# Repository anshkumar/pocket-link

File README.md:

# Pocket Link

A small USB-C adapter that lets a [Pocket](https://pocketide.com) bot hear and speak on an Android
phone's own calls, and (firmware 0.2) tap and type on the phone for it. The phone sees a USB headset, so Android routes the call's audio to it; a second
channel on the same plug carries that audio to the Pocket app, which streams it to the voice engine over
the phone's own internet. No Bluetooth, no Wi-Fi, no battery, nothing stored on the device.

**This is open hardware.** The board, the firmware, the USB protocol and the test tools are here so that
anyone can see exactly what the thing plugged into their phone does, build one, or make it work on a
phone we have not tried.

```
caller ⇄ phone (cellular / WhatsApp call)
           │  Android routes call audio to the "USB headset"
           ▼
   USB-C ⇄ Pocket Link (RP2040)
           │  interface 1–2: USB Audio (UAC 1.0) headset, mic in / headphones out
           │  interface 3:   vendor bulk data channel
           │  interface 4:   HID touch screen + keyboard (firmware 0.2): the app's taps and keystrokes
           ▼
   Pocket app (USB host API) ⇄ WebSocket ⇄ voice engine
```

| Folder | What |
|---|---|
| `revA/` | The first board: KiCad project, Gerbers, BOM, CPL, STEP, schematic PDF, and `source/design.py`, the generator that is the single source of truth. 31 × 16 mm, 4-layer, board-edge USB-C plug. Proven on real calls (Motorola edge 60, Android 16) on 2026-10-08. |
| `revB/` | The next board: the same circuit as a pod on the back of the phone with a short lead, two layers, under ₹500 to build. Plan and cost model; files follow. |
| `firmware/pocket-link-fw/` | RP2040 firmware (Rust): composite USB headset + data channel + HID touch screen/keyboard, 48 kHz ⇄ 16 kHz resampling, the data protocol. Prebuilt `pocket-link-fw.uf2`. |
| `firmware/pocket-link-fw/PROTOCOL.md` | USB descriptors and the app ⇄ adapter packet protocol. The contract the Pocket app implements. |
| `firmware/tools/` | `link_pc_test.py`: status, two-way loopback test and bootloader entry from a Linux PC. `link_input_bench.py`: tap, swipe and type on the phone through the adapter, over adb. |
| `firmware/hosttest/` | USB descriptor dump and validator; resampler frequency response. |
| `firmware/android-test/` | A bare Android test app (Java, no Gradle) that talks to the adapter and a local voice engine. Useful for bring-up on a new phone. |
| `COMPATIBILITY.md` | Which phones work. Please add yours. |

## Build one (DIY)

You do not need our board. Any RP2040 board works for a first test:

1. Hold BOOT and plug a Raspberry Pi Pico or Waveshare RP2040-Zero into a PC; copy `firmware/pocket-link-fw/pocket-link-fw.uf2` onto the `RPI-RP2` drive.
2. Run `python3 firmware/tools/link_pc_test.py status` (needs `pyusb numpy` and the udev rule in `firmware/README.md`). `loopback` must pass both ways.
3. Connect the board to the phone with a USB-C OTG cable, install the Pocket app, open **Account → Voice → Pocket Link**, and set it up. The app recognises the device by its USB identity.

A Pico on an OTG cable is a working Pocket Link. It is also a lever on your phone's port; the pod in `revB/` exists because of that.

## Licences

- Hardware (`revA/`, `revB/`): **CERN-OHL-P-2.0** (`LICENSE-HARDWARE.txt`). Permissive: build it, sell it, change it, keep the notice.
- Firmware, tools and the test app (`firmware/`): **Apache-2.0** (`LICENSE`). `third_party/usbd-audio` is MIT OR Apache-2.0 by its author, with our patches listed in its `PATCHES.md`.
- "Pocket" and "Pocket Link" are names of Pocket; a clone of the design is welcome, a clone of the name is not.

## USB identity

Rev A ships with the pid.codes **test** ID `1209:0001`. Before a public batch we apply for a real PID at
[pid.codes](https://pid.codes), which allocates them to open-source hardware; `PID-REQUEST.md` is the
application. Until then, anything you build with this firmware carries the test ID, which must not be sold.

## Contributing

Phone reports (`COMPATIBILITY.md`), firmware fixes and alternative boards are all welcome; see
`CONTRIBUTING.md`. Bring-up lessons so far: the headphones stream **must be stereo** (a mono USB output
makes Android 16's mixer abort audioserver), and the app should claim the device through a
`USB_DEVICE_ATTACHED` intent filter so Android offers "always" on the permission prompt.

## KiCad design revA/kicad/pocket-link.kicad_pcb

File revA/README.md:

# Pocket Link — rev A

A small USB-C dongle that plugs into the phone. The phone sees it as a **USB headset**,
so Android routes call audio to it. It also exposes a **data channel** that the Pocket app uses to stream
that audio to and from the voice agent over the phone's own internet.
There is no Bluetooth, no Wi-Fi and no battery.

Status: **design complete, DRC clean, not yet fabricated or tested.**

## Size and cost

* PCB **31 × 16 mm**, 0.8 mm thick. With the plug and a shell, about 36 × 18 × 6 mm.
* Parts: **≈ $2.20 (≈ ₹185) per adapter** at LCSC 100-pc prices.
  Prototype run of 5 assembled at JLCPCB is roughly $40–60 total (PCB + setup + parts + shipping).
  Check the real figure in the JLC quote.

## How it works

```
caller ⇄ phone (cellular / WhatsApp call)
           │  Android routes call audio to the "USB headset"
           ▼
   USB-C ⇄ Pocket Link (RP2040)
           │  interface 1: USB Audio (UAC) headset, 16 kHz mono speaker + mic
           │  interface 2: vendor bulk data
           ▼
   Pocket app (USB host API) ⇄ WebSocket ⇄ voice agent
```

The firmware is a TinyUSB composite device:
* Speaker stream (caller's voice) → forwarded to the app on the data interface.
* Data from the app (agent's voice) → played into the microphone stream, so the caller hears the agent.
* The app answers and hangs up calls itself (Android `ANSWER_PHONE_CALLS`). No ADB needed.

## Circuit (see `docs/Pocket-Link-revA-schematic.pdf`)

| Ref | Part | LCSC | Notes |
|---|---|---|---|
| J1 | Molex 105444-0001 USB-C **plug**, board-edge straddle | C134082 | Alt: SHOU HAN TYPE-C 24P GTJB. **Needs 0.8 mm PCB** |
| U1 | RP2040 | C2040 | USB 1.1 device. Support circuit per the RP2040 hardware design guide |
| U2 | W25Q16JVSNIQ 2 MB QSPI flash | C2456211 | Firmware |
| U3 | AP2112K-3.3 LDO | C51118 | Phone VBUS → 3.3 V, about 25 mA load |
| U4 | USBLC6-2SC6 | C7519 | ESD on D+/D− |
| Y1 | 12 MHz 3225 crystal + 2 × 33 pF, 1 kΩ on XOUT | C9002 | |
| R1 | 5.1 kΩ on CC | C25905 | Tells the phone a USB device is attached, so it supplies 5 V |
| D1 | Green status LED (GPIO25) | C72043 | |
| TP1–3 | Back-side pads: BOOT, GND, 3V3 | — | |

The SWD debug pins are not brought out. Firmware loads over USB, and debugging happens on any
RP2040 dev board running the same firmware.

## Board

* 4 layers, **0.8 mm**: L1 signal, L2 GND, L3 +3V3, L4 signal + GND pour.
* 0.1 mm min clearance and 0.127 mm min track. Both are within JLCPCB's standard 4-layer capability. The
  USB-C plug's 0.5 mm-pitch pads need this.
* 0.3 / 0.6 mm vias. 5 vias in the RP2040 ground pad.
* Verification (`docs/verification.txt`):
  * schematic and PCB both match `source/design.py` (21 nets, 34 parts)
  * KiCad DRC: **0 violations, 0 unconnected**
  * Gerbers re-read independently: 11 layers, outline 31 × 16 mm

## Ordering (JLCPCB)

1. Gerbers: `fab/Pocket-Link-revA-gerbers.zip`. Settings: 4 layers, **0.8 mm thickness**, JLC04081H-3313 stackup (or
   whatever JLC offers for 0.8 mm 4-layer), ENIG recommended for the fine-pitch plug and QFN.
2. Assembly (top side): `fab/BOM_JLCPCB.csv` + `fab/CPL_JLCPCB.csv`. **Check rotations in JLC's preview**,
   especially U1 pin 1, U2, U3, U4, Y1 and D1.
3. **The USB-C plug J1 is not in the JLC BOM or CPL.** It straddles the board edge with pads on both sides,
   so solder it after assembly (hand or hot-air), or ask JLC for manual soldering. Order C134082 along with the
   boards.
4. Small boards: ask JLC to panelize (e.g. 2 × 3) to stay above their minimum assembly size.

## First power-up

1. Plug into a Linux PC first (USB-C to USB-C cable, or a USB-A to USB-C female adapter). A blank board
   shows up as the **RPI-RP2** drive. Drag the firmware `.uf2` onto it.
2. `lsusb` / `aplay -l` should show a USB audio card plus the vendor interface. Run a PC loopback test.
3. Plug into the Motorola, install the Pocket test app, and call it from the allowed number.
4. To re-enter the bootloader later: short **BT** to **G** on the back while plugging in.

## Risks / next steps

| Risk | Plan |
|---|---|
| Whether the app can use the data interface while Android uses the audio part | First firmware test. Fallbacks need firmware changes only (e.g. a HID data channel) |
| Some phones need special USB audio formats (48 kHz) | Firmware offers 48 kHz too and resamples internally |
| Charging through the adapter (v2) | Needs a USB-PD pass-through controller and a female USB-C. Planned for rev B |
| Enclosure | A simple 2-part shell like a USB-C to 3.5 mm adapter, next step after the board fits |

## Files

* `kicad/`: KiCad 7 project with schematic, PCB and local footprints (QFN-56 with 0.3 mm vias)
* `fab/`: Gerbers + drill files, JLC BOM/CPL, full BOM with MPNs and cost, STEP 3D model
* `docs/`: schematic PDF, assembly + layer PDF, top/bottom previews, DRC report, verification results
* `source/`: Python generators. `design.py` is the single source of truth

## Cost reality check (PCB Power quote INQ649465, 7 Oct 2026, 6 boards)

| Line | Quote | Per board | Why |
|---|---|---|---|
| PCB fabrication (4-layer, 0.8 mm, ENIG, 2 panels of 3) | ₹6,966 | ₹1,161 | Panel NRE spread over 6 boards; a 2-layer board would roughly halve this |
| Assembly (30 SMD + 1 QFN, top side) | ₹3,132 | ₹522 | Reasonable for a tiny run |
| Component sourcing (turnkey) | ₹8,950 | ₹1,492 | The outlier. Parts are ≈ $2.20 (≈ ₹185) per board at LCSC; the quote carries minimum pack quantities (32 × 33 pF for 12 used), "independent supplier" markups on the RP2040, flash, crystal and passives (no warranty, 3–5 week lead), one part from Robu, and the LED was **not available and not priced** |
| Total before GST | ₹19,048 | ₹3,175 | ≈ ₹3,750 per adapter with GST, for six |

So the BOM is not the problem; the sourcing route and the batch size are. What to do:

1. **Consign the parts.** Order one LCSC/DigiKey basket yourself (10 sets ≈ ₹1,500 shipped, every part in stock, warranted) and give PCB Power assembly only. That alone cuts the per-board cost from ₹3,175 to about ₹1,900.
2. **Or order at JLCPCB** with the files in `fab/` (4-layer 0.8 mm ENIG, 5 boards + assembly ≈ $40–60 all in, plus Indian customs ≈ ₹1,000–1,500): roughly a quarter of the PCB Power price for the same six boards, because the parts come from their own LCSC shelf.
3. **Rev B goes to two layers** (the board-edge plug is the only reason for four) and a pre-molded cable-mount plug, which removes the one hand-soldered part. Fabrication then drops to the ₹300–500 per board range in tens, and under ₹100 in hundreds.
4. **Don't change the MCU for cost yet.** RP2040 + flash + crystal are ₹90 of the ₹185 parts; CH32X035 saves about ₹60 a board at the price of a firmware port. Worth it at a thousand units, and then for its on-chip USB-PD PHY (charge-through in rev C), not for the ₹60.

## Carrying it without breaking it (stopgap for rev A)

Rev A is a 36 mm rigid body hanging off the phone's USB-C receptacle: a 10 N snag at the tip is a 0.36 N·m moment on the port, enough to crack the plug or the phone's socket. Until rev B (pod on the back of the phone, 6–8 cm lead with strain relief), ship every rev A with a short **USB-C male-to-female extension (≈ 10 cm)**. USB audio and the vendor bulk channel pass through an extension; the dongle then hangs on a cable instead of a lever. Rev C adds a USB-C female for charge-through (PD power-role swap; CH32X035 has the PD PHY on chip).

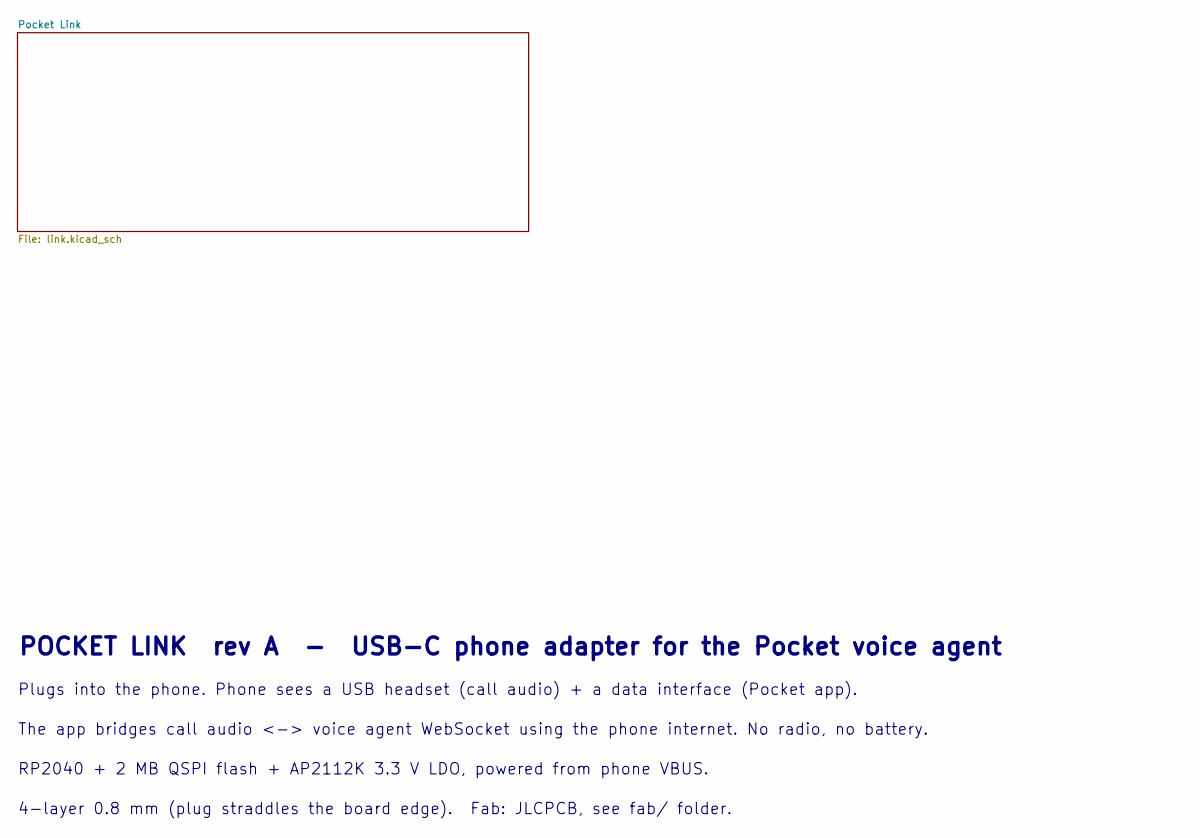
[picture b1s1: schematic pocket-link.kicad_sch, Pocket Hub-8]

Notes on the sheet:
POCKET LINK rev A - USB-C phone adapter for the Pocket voice agent
Plugs into the phone. Phone sees a USB headset (call audio) + a data interface (Pocket app).
The app bridges call audio <-> voice agent WebSocket using the phone internet. No radio, no battery.
RP2040 + 2 MB QSPI flash + AP2112K 3.3 V LDO, powered from phone VBUS.
4-layer 0.8 mm (plug straddles the board edge). Fab: JLCPCB, see fab/ folder.

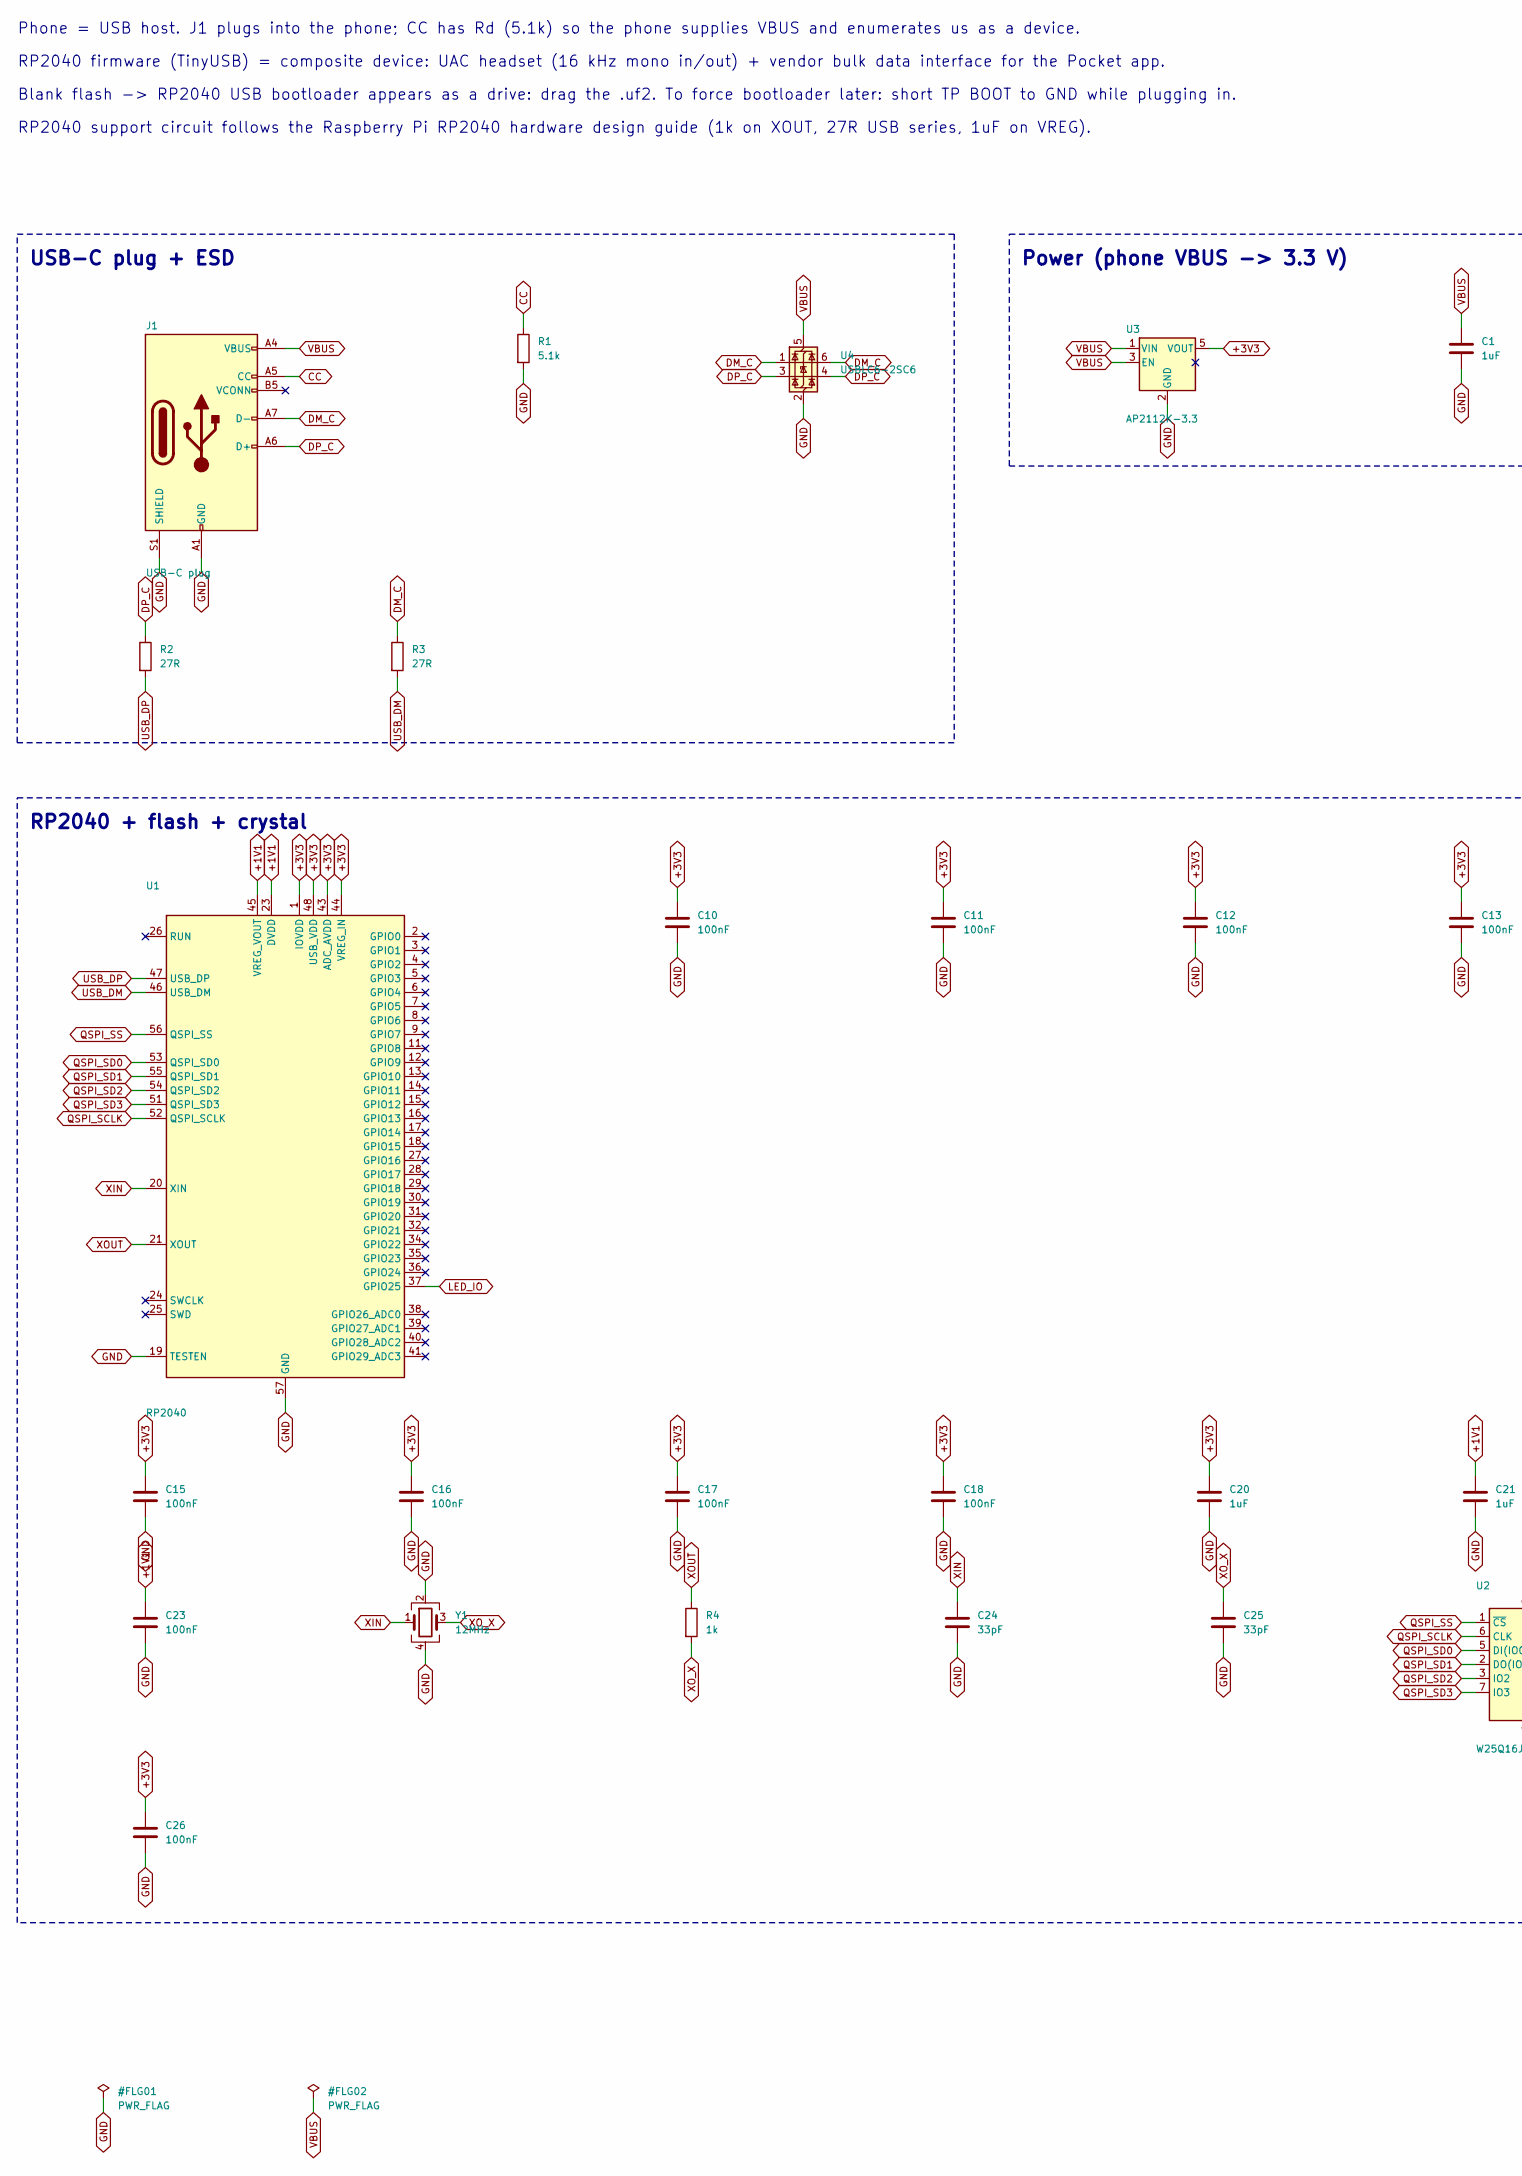
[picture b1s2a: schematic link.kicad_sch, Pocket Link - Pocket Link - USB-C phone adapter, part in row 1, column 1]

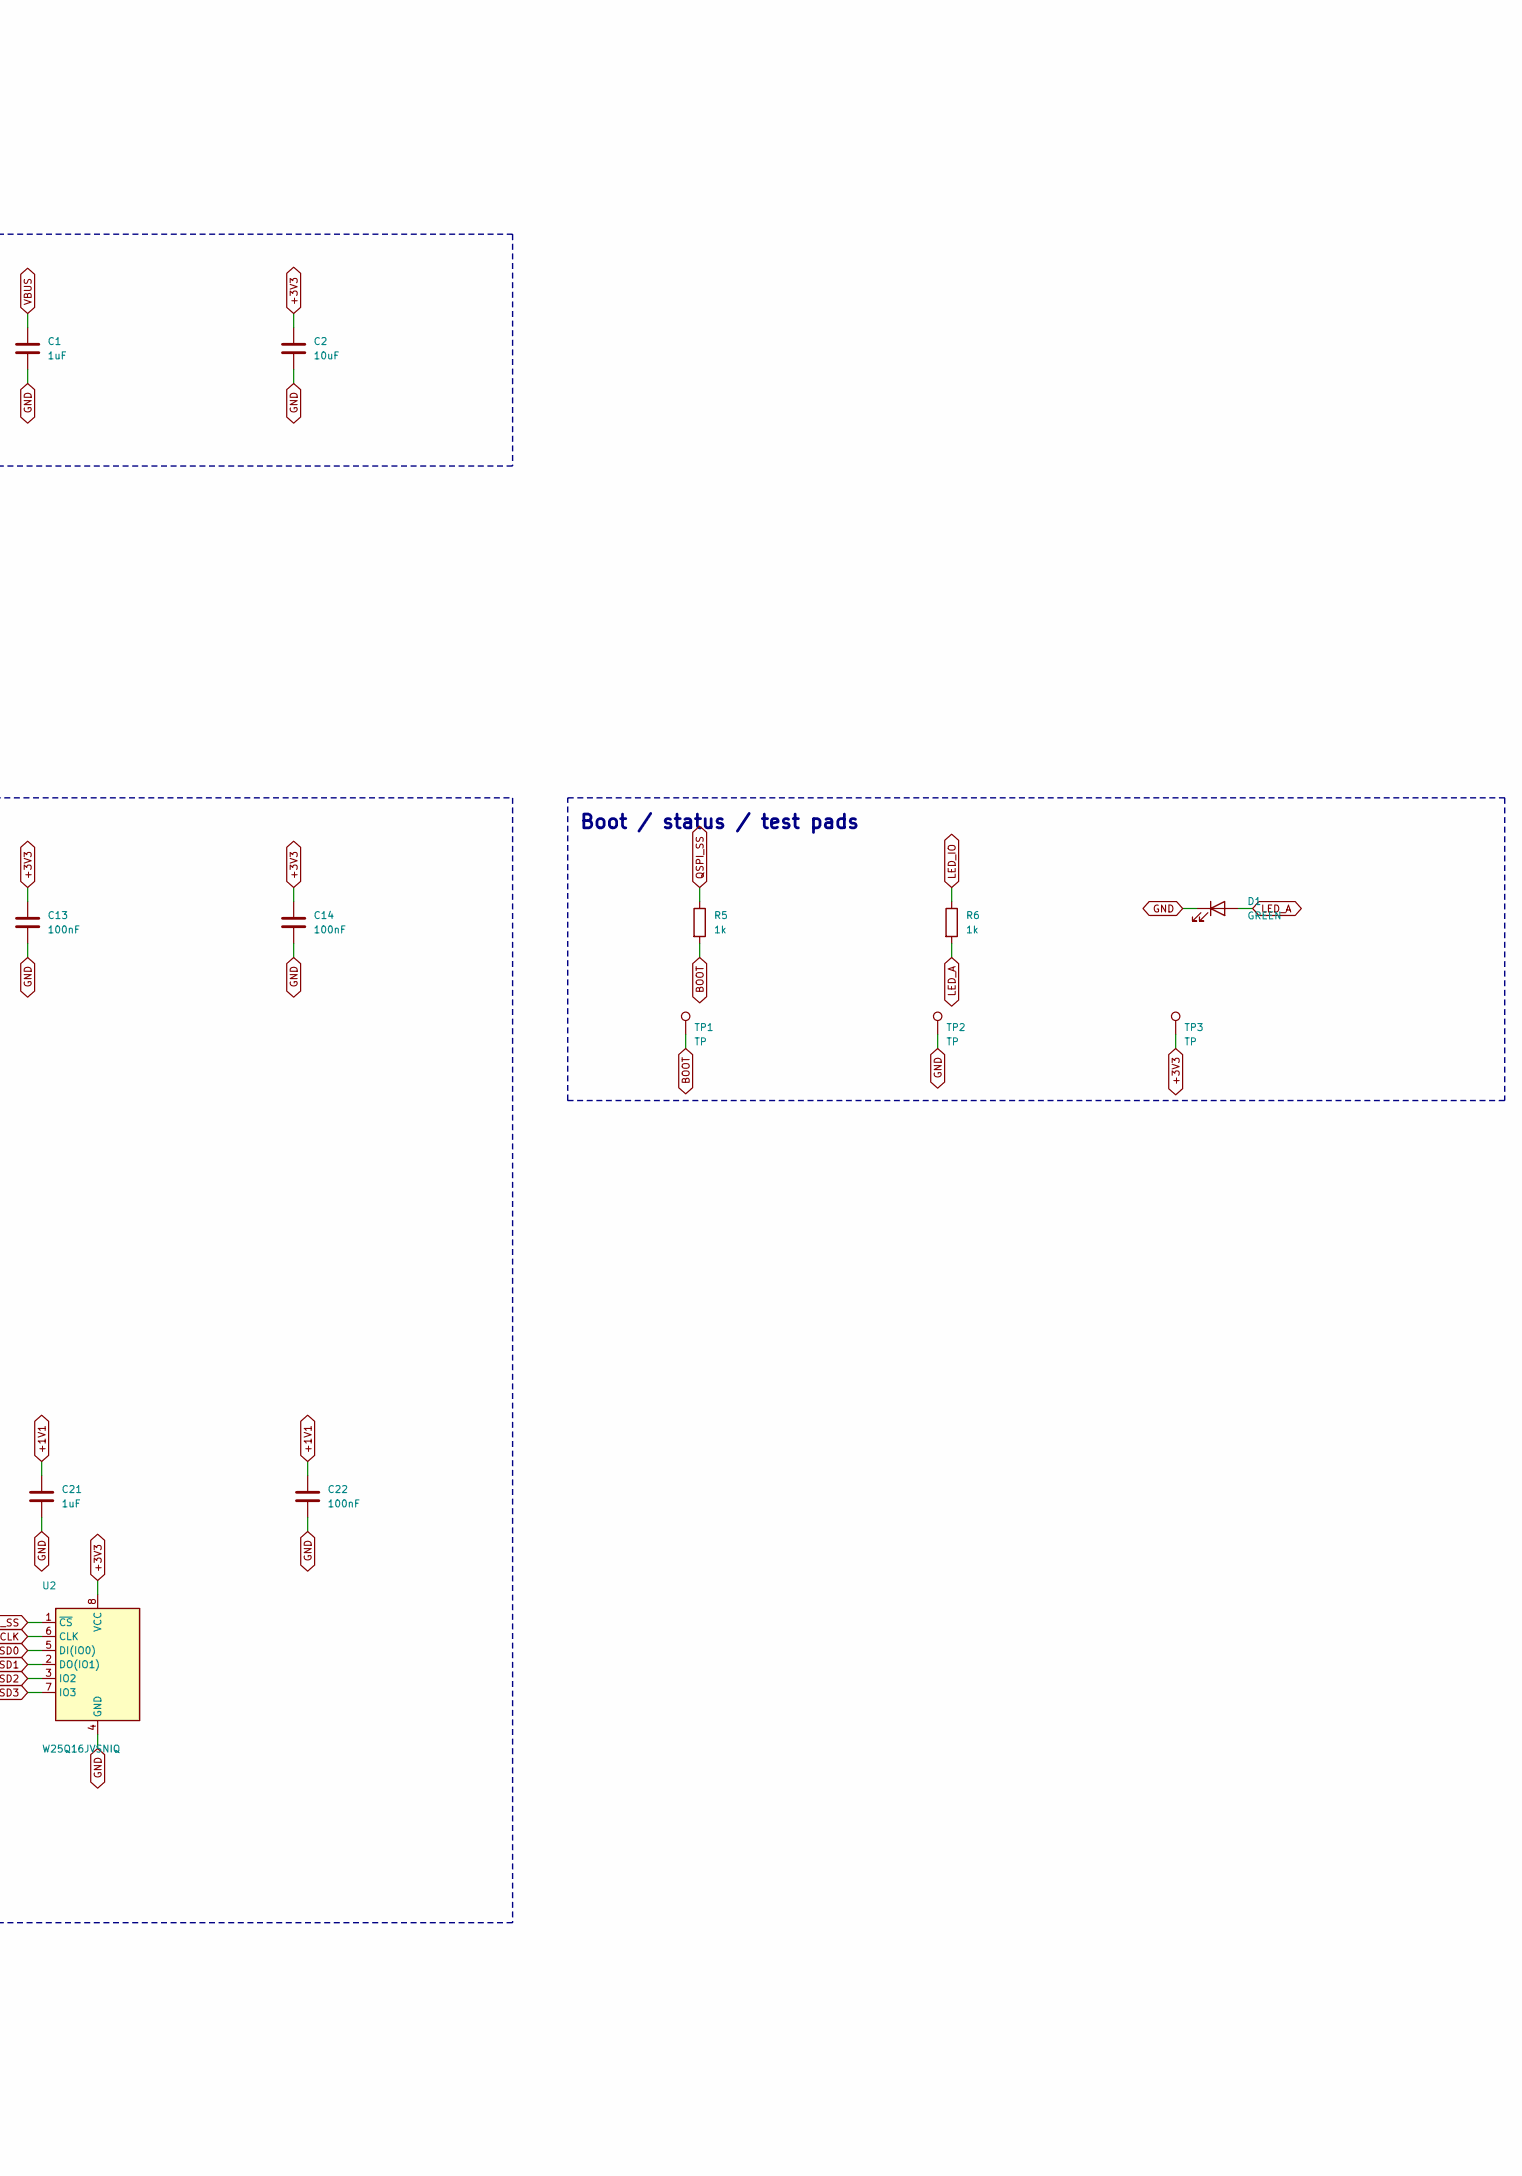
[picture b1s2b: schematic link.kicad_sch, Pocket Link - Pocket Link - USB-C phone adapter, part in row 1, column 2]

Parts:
C1, C20, C21: 1uF; C_0402_1005Metric; MPN CL05A105KA5NQNC; LCSC C52923
C2: 10uF; C_0603_1608Metric; MPN CL10A106KP8NNNC; LCSC C19702
C10, C11, C12, C13, C14, C15, C16, C17, C18, C22, C23, C26: 100nF; C_0402_1005Metric; MPN CL05B104KO5NNNC; LCSC C1525
C24, C25: 33pF; C_0402_1005Metric; MPN 0402CG330J500NT; LCSC C1562
D1: GREEN; LED_0603_1608Metric; MPN 19-217/GHC-YR1S2/3T; LCSC C72043
J1: USB-C plug; USB_C_Plug_Molex_105444; MPN 105444-0001; LCSC C134082
R1: 5.1k; R_0402_1005Metric; MPN 0402WGF5101TCE; LCSC C25905
R2, R3: 27R; R_0402_1005Metric; MPN 0402WGF270JTCE; LCSC C25100
R4, R5, R6: 1k; R_0402_1005Metric; MPN 0402WGF1001TCE; LCSC C11702
TP1, TP2, TP3: TP; TestPoint_Pad_D1.0mm
U1: RP2040; QFN-56-1EP_7x7mm_P0.4mm_EP3.2x3.2mm_Vias0.3; MPN RP2040; LCSC C2040
U2: W25Q16JVSNIQ; SOIC-8_3.9x4.9mm_P1.27mm; MPN W25Q16JVSNIQ; LCSC C2456211
U3: AP2112K-3.3; SOT-23-5; MPN AP2112K-3.3TRG1; LCSC C51118
U4: USBLC6-2SC6; SOT-23-6; MPN USBLC6-2SC6; LCSC C7519
Y1: 12MHz; Crystal_SMD_3225-4Pin_3.2x2.5mm; MPN X322512MSB4SI; LCSC C9002

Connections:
+1V1: C21.1, C22.1, C23.1, U1.23 (DVDD), U1.45 (VREG_VOUT), U1.50 (DVDD)
+3V3: C2.1, C10.1, C11.1, C12.1, C13.1, C14.1, C15.1, C16.1, C17.1, C18.1, C20.1, C26.1, TP3.1, U1.1 (IOVDD), U1.10 (IOVDD), U1.22 (IOVDD), U1.33 (IOVDD), U1.42 (IOVDD), U1.43 (ADC_AVDD), U1.44 (VREG_IN), U1.48 (USB_VDD), U1.49 (IOVDD), U2.8 (VCC), U3.5 (VOUT)
BOOT: R5.2, TP1.1
CC: J1.A5 (CC), R1.1
DM_C: J1.A7 (D-), R3.1, U4.1 (I/O1), U4.6 (I/O1)
DP_C: J1.A6 (D+), R2.1, U4.3 (I/O2), U4.4 (I/O2)
GND: C1.2, C2.2, C10.2, C11.2, C12.2, C13.2, C14.2, C15.2, C16.2, C17.2, C18.2, C20.2, C21.2, C22.2, C23.2, C24.2, C25.2, C26.2, D1.1 (K), J1.A1 (GND), J1.A12 (GND), J1.B1 (GND), J1.B12 (GND), J1.S1 (SHIELD), R1.2, TP2.1, U1.19 (TESTEN), U1.57 (GND), U2.4 (GND), U3.2 (GND), U4.2 (GND), Y1.2, Y1.4
LED_A: D1.2 (A), R6.2
LED_IO: R6.1, U1.37 (GPIO25)
QSPI_SCLK: U1.52 (QSPI_SCLK), U2.6 (CLK)
QSPI_SD0: U1.53 (QSPI_SD0), U2.5 (DI(IO0))
QSPI_SD1: U1.55 (QSPI_SD1), U2.2 (DO(IO1))
QSPI_SD2: U1.54 (QSPI_SD2), U2.3 (IO2)
QSPI_SD3: U1.51 (QSPI_SD3), U2.7 (IO3)
QSPI_SS: R5.1, U1.56 (QSPI_SS), U2.1 (~CS)
USB_DM: R3.2, U1.46 (USB_DM)
USB_DP: R2.2, U1.47 (USB_DP)
VBUS: C1.1, J1.A4 (VBUS), J1.A9 (VBUS), J1.B4 (VBUS), J1.B9 (VBUS), U3.1 (VIN), U3.3 (EN), U4.5 (VBUS)
XIN: C24.1, U1.20 (XIN), Y1.1
XOUT: R4.1, U1.21 (XOUT)
XO_X: C25.1, R4.2, Y1.3

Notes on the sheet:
Phone = USB host. J1 plugs into the phone; CC has Rd (5.1k) so the phone supplies VBUS and enumerates us as a device.
RP2040 firmware (TinyUSB) = composite device: UAC headset (16 kHz mono in/out) + vendor bulk data interface for the Pocket app.
Blank flash -> RP2040 USB bootloader appears as a drive: drag the .uf2. To force bootloader later: short TP BOOT to GND while plugging in.
RP2040 support circuit follows the Raspberry Pi RP2040 hardware design guide (1k on XOUT, 27R USB series, 1uF on VREG).
USB-C plug + ESD
Power (phone VBUS -> 3.3 V)
RP2040 + flash + crystal
Boot / status / test pads

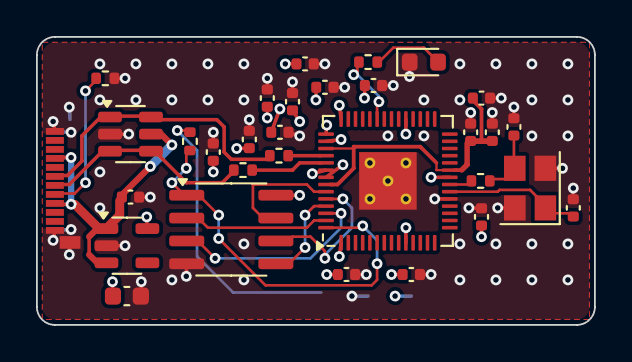
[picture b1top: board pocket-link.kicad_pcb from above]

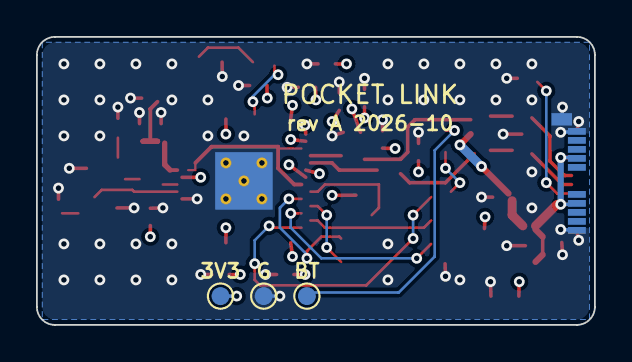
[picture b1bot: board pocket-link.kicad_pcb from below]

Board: 4 copper layers, 31.0 x 16.0 mm, 34 parts (3 on the bottom side), 21 nets.

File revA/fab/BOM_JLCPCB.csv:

Comment,Designator,Footprint,LCSC Part #
5.1k,R1,R_0402_1005Metric,C25905
USBLC6-2SC6,U4,SOT-23-6,C7519
27R,"R2,R3",R_0402_1005Metric,C25100
AP2112K-3.3,U3,SOT-23-5,C51118
1uF,"C1,C20,C21",C_0402_1005Metric,C52923
10uF,C2,C_0603_1608Metric,C19702
RP2040,U1,QFN-56-1EP_7x7mm_P0.4mm_EP3.2x3.2mm_Vias0.3,C2040
100nF,"C10,C11,C12,C13,C14,C15,C16,C17,C18,C22,C23,C26",C_0402_1005Metric,C1525
12MHz,Y1,Crystal_SMD_3225-4Pin_3.2x2.5mm,C9002
1k,"R4,R5,R6",R_0402_1005Metric,C11702
33pF,"C24,C25",C_0402_1005Metric,C1562
W25Q16JVSNIQ,U2,SOIC-8_3.9x4.9mm_P1.27mm,C2456211
GREEN,D1,LED_0603_1608Metric,C72043
